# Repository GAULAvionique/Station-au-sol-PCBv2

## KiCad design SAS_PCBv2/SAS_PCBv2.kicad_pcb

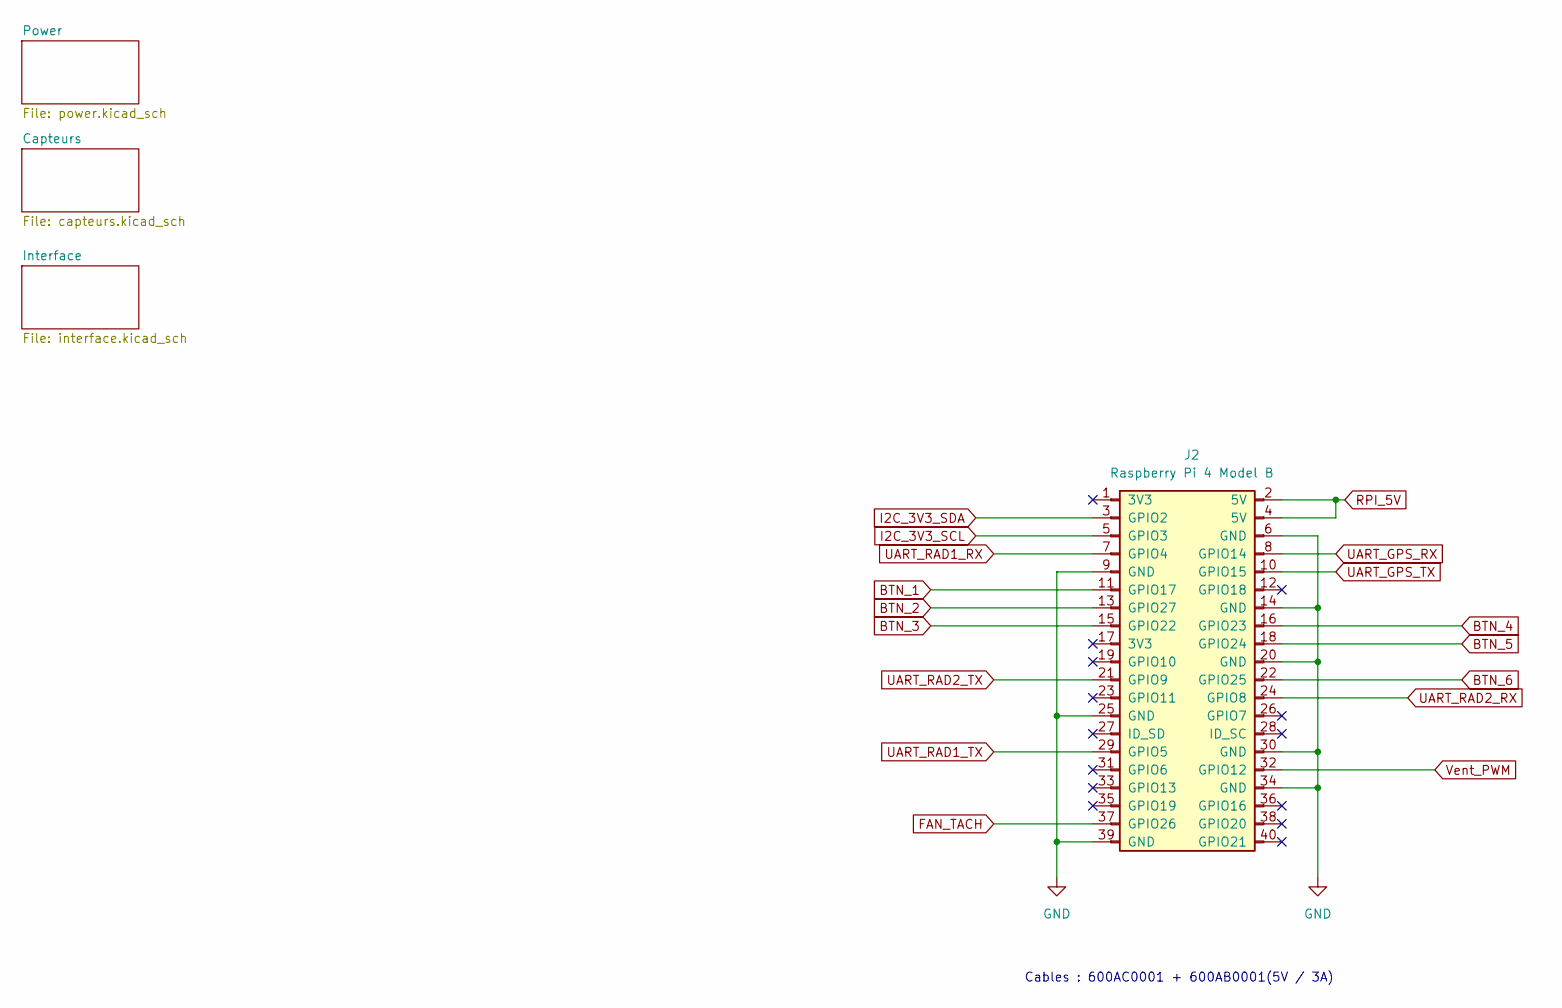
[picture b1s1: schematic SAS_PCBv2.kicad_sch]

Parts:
J2: Raspberry Pi 4 Model B; PinSocket_2x20_P2.54mm_Vertical

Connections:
BTN_1: J2.11 (GPIO17); also elsewhere on the board
BTN_2: J2.13 (GPIO27); also elsewhere on the board
BTN_3: J2.15 (GPIO22); also elsewhere on the board
BTN_4: J2.16 (GPIO23); also elsewhere on the board
BTN_5: J2.18 (GPIO24); also elsewhere on the board
BTN_6: J2.22 (GPIO25); also elsewhere on the board
FAN_TACH: J2.37 (GPIO26); also elsewhere on the board
GND: J2.6 (GND), J2.9 (GND), J2.14 (GND), J2.20 (GND), J2.25 (GND), J2.30 (GND), J2.34 (GND), J2.39 (GND); also elsewhere on the board
I2C_3V3_SCL: J2.5 (GPIO3); also elsewhere on the board
I2C_3V3_SDA: J2.3 (GPIO2); also elsewhere on the board
RPI_5V: J2.2 (5V), J2.4 (5V); also elsewhere on the board
UART_GPS_RX: J2.8 (GPIO14); also elsewhere on the board
UART_GPS_TX: J2.10 (GPIO15); also elsewhere on the board
UART_RAD1_RX: J2.7 (GPIO4); also elsewhere on the board
UART_RAD1_TX: J2.29 (GPIO5); also elsewhere on the board
UART_RAD2_RX: J2.24 (GPIO8); also elsewhere on the board
UART_RAD2_TX: J2.21 (GPIO9); also elsewhere on the board
Vent_PWM: J2.32 (GPIO12); also elsewhere on the board

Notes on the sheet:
Cables : 600AC0001 + 600AB0001(5V / 3A)

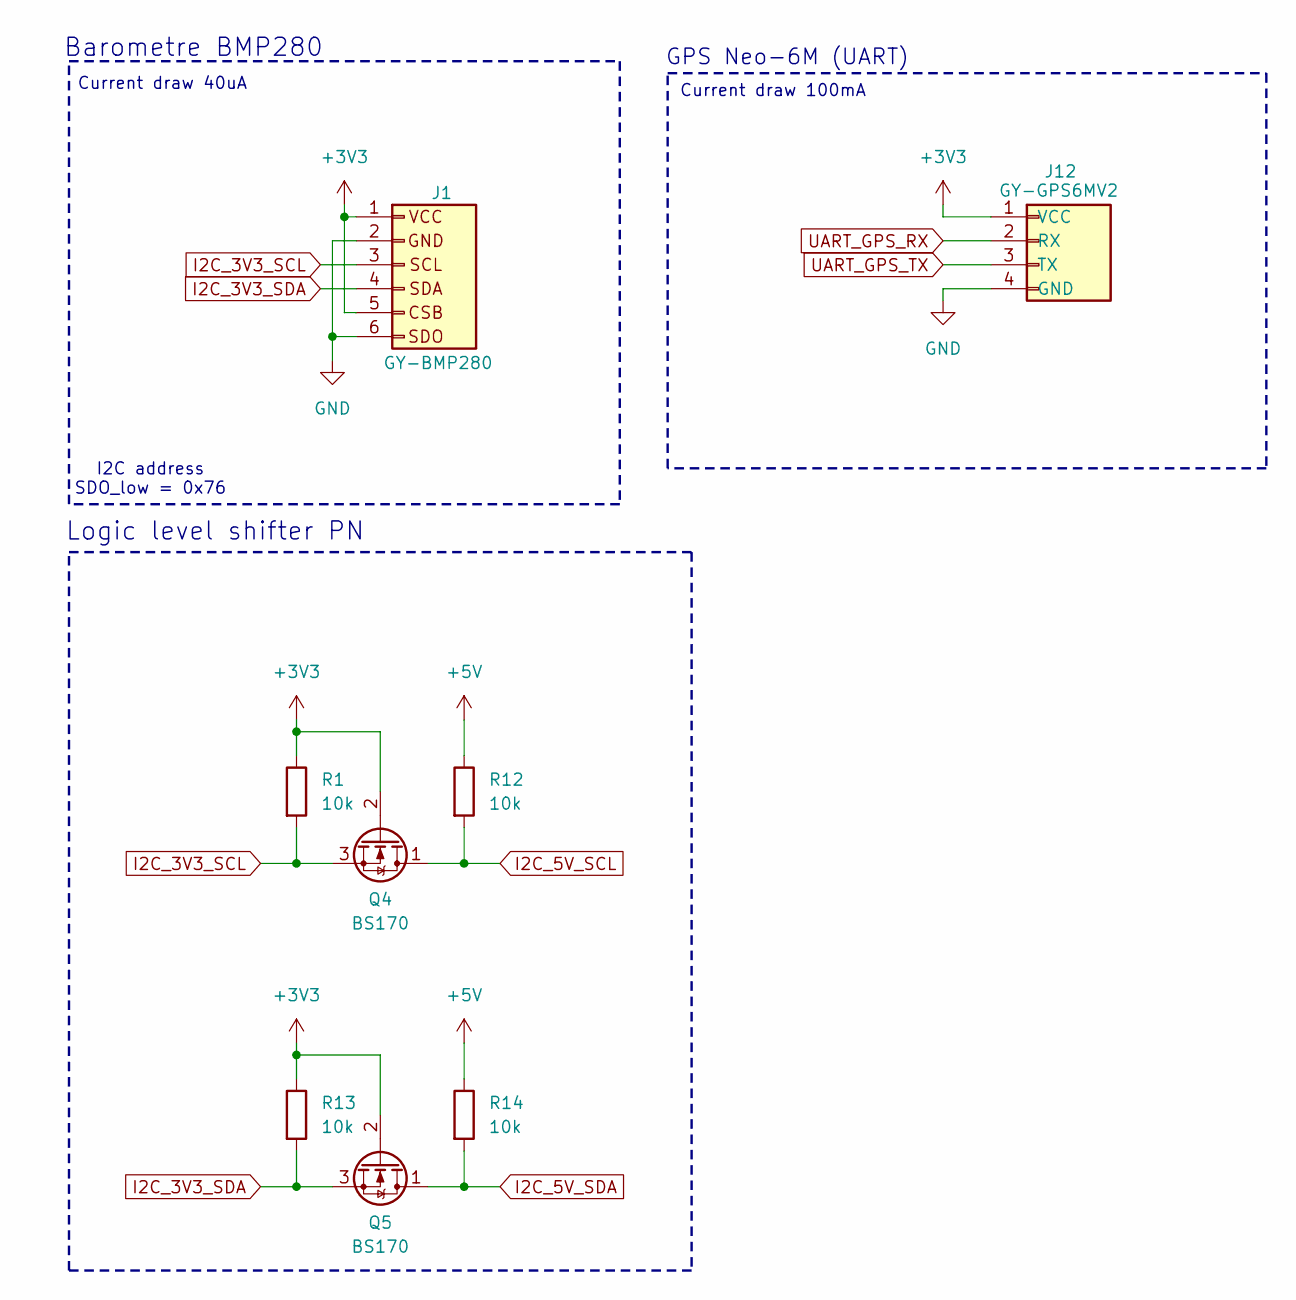
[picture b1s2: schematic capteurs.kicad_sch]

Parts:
J1: GY-BMP280; PinHeader_1x06_P2.54mm_Vertical
J12: GY-GPS6MV2; PinHeader_1x04_P2.54mm_Vertical
Q4, Q5: BS170; TO-92_Inline
R1, R12, R13, R14: 10k; R_Axial_DIN0207_L6.3mm_D2.5mm_P10.16mm_Horizontal; Digikey MFR-25FRF52-10K

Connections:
+3V3: J1.1 (Vcc), J1.5, J12.1 (VCC), Q4.2 (G), Q5.2 (G), R1.1, R13.1; also elsewhere on the board
+5V: R12.1, R14.1; also elsewhere on the board
GND: J1.2, J1.6, J12.4 (GND); also elsewhere on the board
I2C_3V3_SCL: J1.3, Q4.3 (S), R1.2; also elsewhere on the board
I2C_3V3_SDA: J1.4, Q5.3 (S), R13.2; also elsewhere on the board
I2C_5V_SCL: Q4.1 (D), R12.2; also elsewhere on the board
I2C_5V_SDA: Q5.1 (D), R14.2; also elsewhere on the board
UART_GPS_RX: J12.2 (RX); also elsewhere on the board
UART_GPS_TX: J12.3 (TX); also elsewhere on the board

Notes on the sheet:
Current draw 40uA
Logic level shifter PN
GPS Neo-6M (UART)
I2C address SDO_low = 0x76
Barometre BMP280
Current draw 100mA

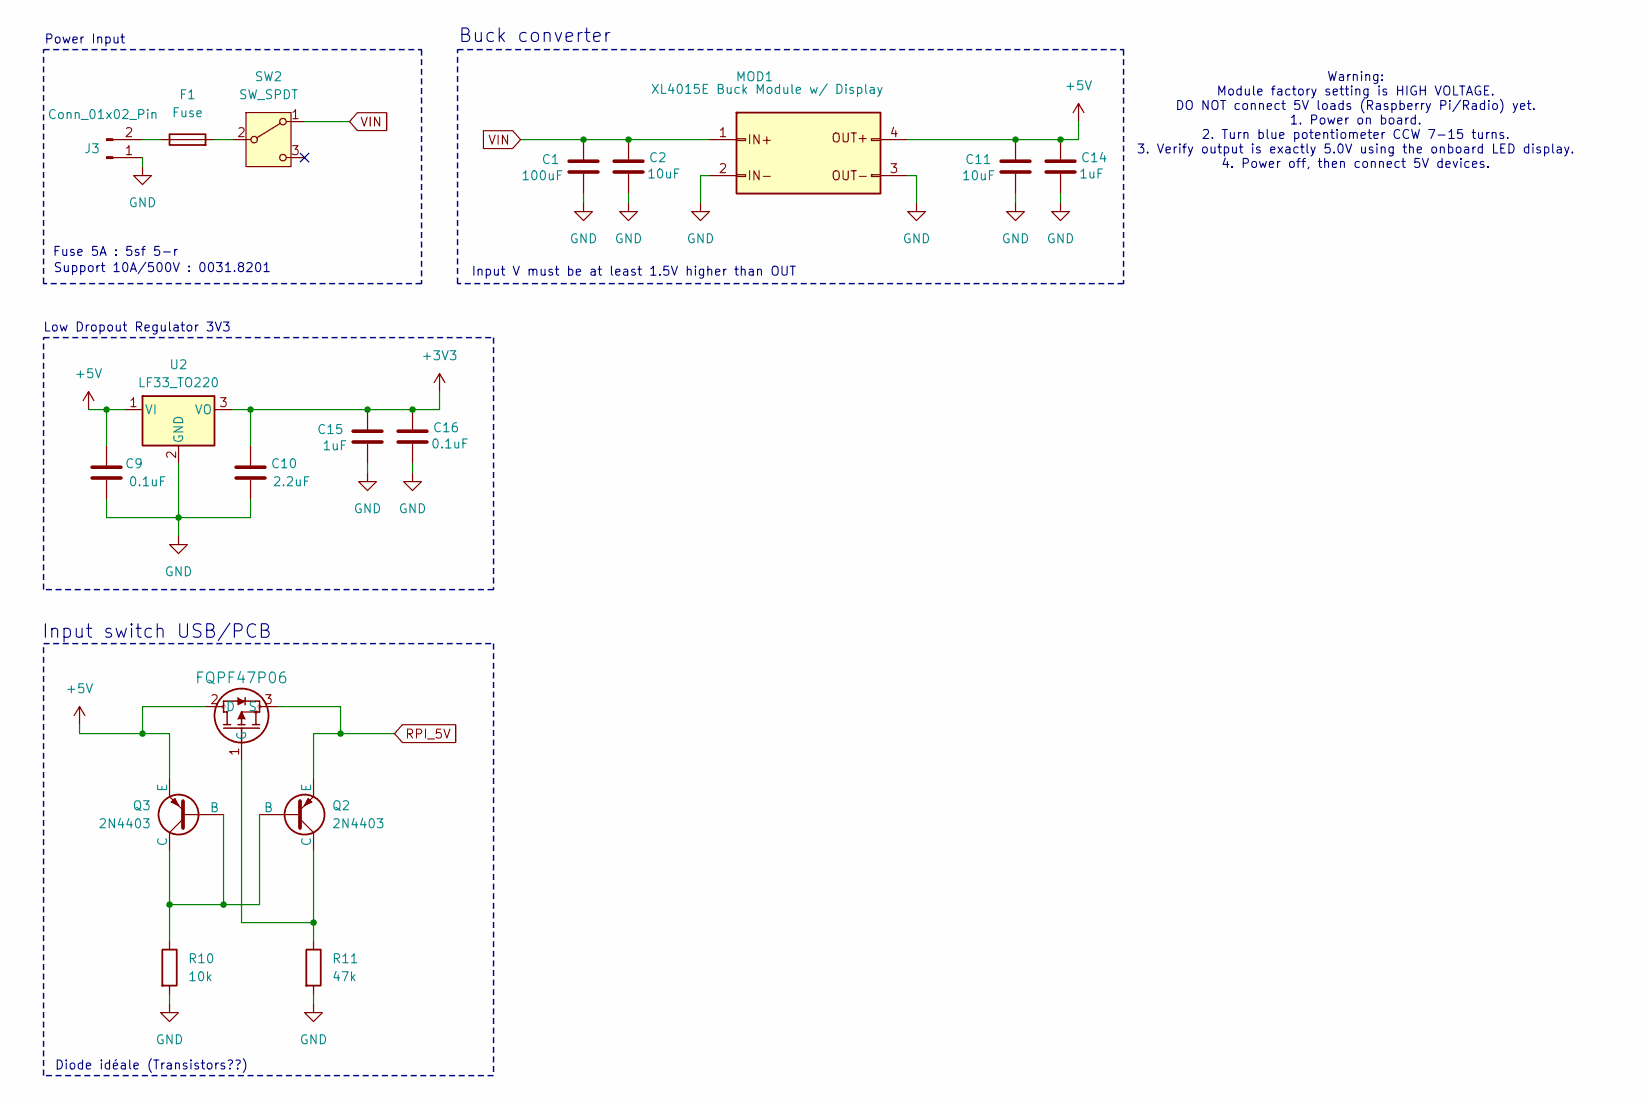
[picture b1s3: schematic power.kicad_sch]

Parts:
C1: 100uF; CAP_RR71_NIC
C2, C11: 10uF; CP_Radial_D5.0mm_P2.00mm; Digikey 1189-2322-ND
C9, C16: 0.1uF; CAP_C320_KEM
C10: 2.2uF; CAP_FG14_TDK
C14, C15: 1uF; CP_Radial_D5.0mm_P2.00mm
F1: Fuse; Fuseholder_Cylinder-5x20mm_Schurter_0031_8201_Horizontal_Op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
J3: Conn_01x02_Pin; AMASS_XT30U-M_1x02_P5.0mm_Vertical
MOD1: XL4015E Buck Module w/ Display; XL4015E_Buck_Module_68x38mm(1)
MOSFET1: FQPF47P06; PMOS_FQP_ONS
Q2, Q3: 2N4403; PBIP_2N4403_DIO
R10: 10k; R_Axial_DIN0207_L6.3mm_D2.5mm_P10.16mm_Horizontal; Digikey MFR-25FRF52-10K
R11: 47k; R_Axial_DIN0207_L6.3mm_D2.5mm_P10.16mm_Horizontal; Digikey MFR-25FRF52-47K
SW2: SW_SPDT; SW_ANT1_CRS
U2: LF33_TO220; TO-220-3_Vertical

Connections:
+3V3: C10.1, C15.1, C16.1, U2.3 (VO); also elsewhere on the board
+5V: C9.1, C11.1, C14.1, MOD1.4 (OUT+), MOSFET1.2 (D), Q3.1 (E), U2.1 (VI); also elsewhere on the board
GND: C1.2, C2.2, C9.2, C10.2, C11.2, C14.2, C15.2, C16.2, J3.1, MOD1.2 (IN-), MOD1.3 (OUT-), R10.2, R11.2, U2.2 (GND); also elsewhere on the board
unnamed: F1.1, J3.2
unnamed: MOSFET1.1 (G), Q2.3 (C), R11.1
unnamed: Q2.2 (B), Q3.2 (B), Q3.3 (C), R10.1
unnamed: F1.2, SW2.2 (B)
RPI_5V: MOSFET1.3 (S), Q2.1 (E); also elsewhere on the board
VIN: C1.1, C2.1, MOD1.1 (IN+), SW2.1 (A)

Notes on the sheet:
Fuse 5A : 5sf 5-r
Low Dropout Regulator 3V3
Support 10A/500V : 0031.8201
Diode idéale (Transistors??)
Input switch USB/PCB
Input V must be at least 1.5V higher than OUT
Power Input
Buck converter
Warning: Module factory setting is HIGH VOLTAGE. DO NOT connect 5V loads (Raspberry Pi/Radio) yet. 1. Power on board. 2. Turn blue potentiometer CCW 7-15 turns. 3. Verify output is exactly 5.0V using the onboard LED display. 4. Power off, then connect 5V devices.

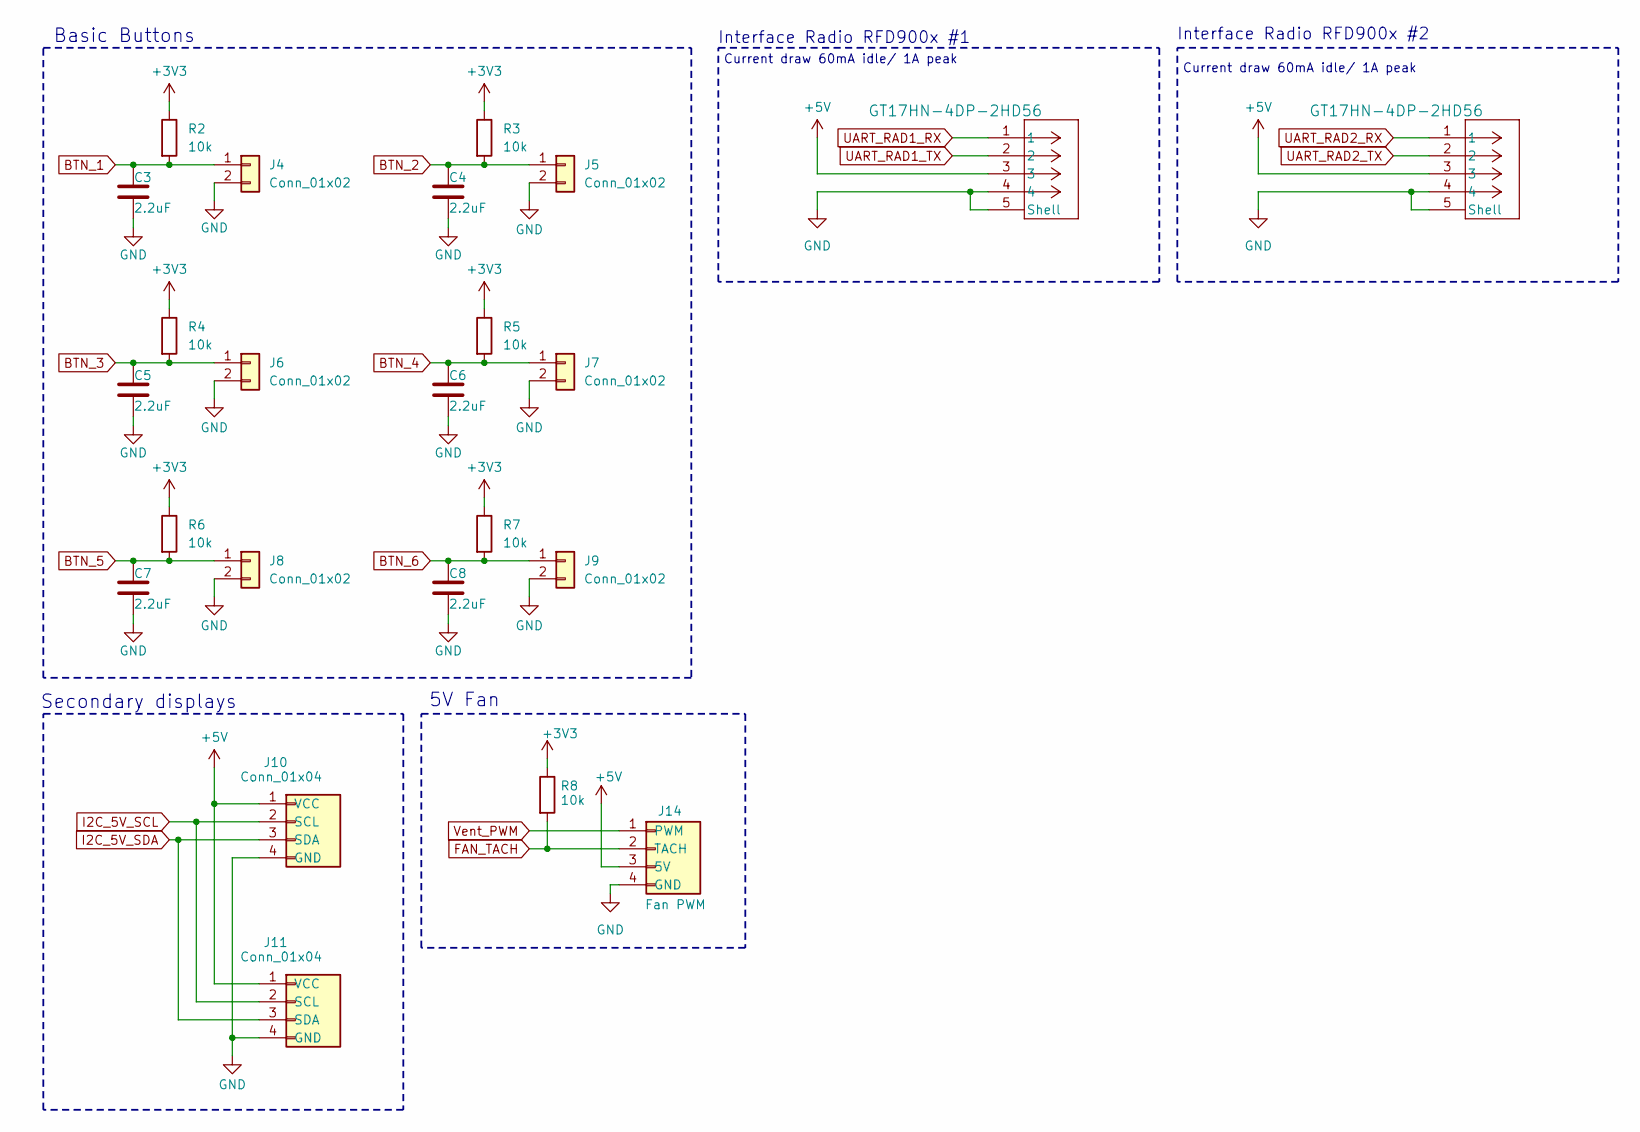
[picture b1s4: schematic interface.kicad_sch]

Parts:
C3, C4, C5, C6, C7, C8: 2.2uF; CAP_FG14_TDK
J4, J5, J6, J7, J8, J9: Conn_01x02; PinHeader_1x02_P2.54mm_Vertical
J10, J11: Conn_01x04; PinHeader_1x04_P2.54mm_Vertical
J14: Fan PWM; PinHeader_1x04_P2.54mm_Vertical
J16, J17: GT17HN-4DP-2HD56; CONN4_GT17HN_HIR; Manufacturer_Part_Number GT17HN-4DP-2H(D)(56); DigiKey_Part_Number 26-GT17HN-4DP-2H(D)(56)-ND
R2, R3, R4, R5, R6, R7, R8: 10k; R_Axial_DIN0207_L6.3mm_D2.5mm_P10.16mm_Horizontal; Digikey MFR-25FRF52-10K

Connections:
+3V3: R2.1, R3.1, R4.1, R5.1, R6.1, R7.1, R8.1; also elsewhere on the board
+5V: J10.1 (VCC), J11.1 (VCC), J14.3 (5V), J16.3, J17.3; also elsewhere on the board
BTN_1: C3.1, J4.1, R2.2; also elsewhere on the board
BTN_2: C4.1, J5.1, R3.2; also elsewhere on the board
BTN_3: C5.1, J6.1, R4.2; also elsewhere on the board
BTN_4: C6.1, J7.1, R5.2; also elsewhere on the board
BTN_5: C7.1, J8.1, R6.2; also elsewhere on the board
BTN_6: C8.1, J9.1, R7.2; also elsewhere on the board
FAN_TACH: J14.2 (TACH), R8.2; also elsewhere on the board
GND: C3.2, C4.2, C5.2, C6.2, C7.2, C8.2, J4.2, J5.2, J6.2, J7.2, J8.2, J9.2, J10.4 (GND), J11.4 (GND), J14.4 (GND), J16.4, J16.5 (Shell), J16.6 (Shell), J16.7 (Shell), J16.8 (Shell), J17.4, J17.5 (Shell), J17.6 (Shell), J17.7 (Shell), J17.8 (Shell); also elsewhere on the board
I2C_5V_SCL: J10.2 (SCL), J11.2 (SCL); also elsewhere on the board
I2C_5V_SDA: J10.3 (SDA), J11.3 (SDA); also elsewhere on the board
UART_RAD1_RX: J16.1; also elsewhere on the board
UART_RAD1_TX: J16.2; also elsewhere on the board
UART_RAD2_RX: J17.1; also elsewhere on the board
UART_RAD2_TX: J17.2; also elsewhere on the board
Vent_PWM: J14.1 (PWM); also elsewhere on the board

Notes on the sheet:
5V Fan
Current draw 60mA idle/ 1A peak
Secondary displays
Interface Radio RFD900x #2
Basic Buttons
Interface Radio RFD900x #1

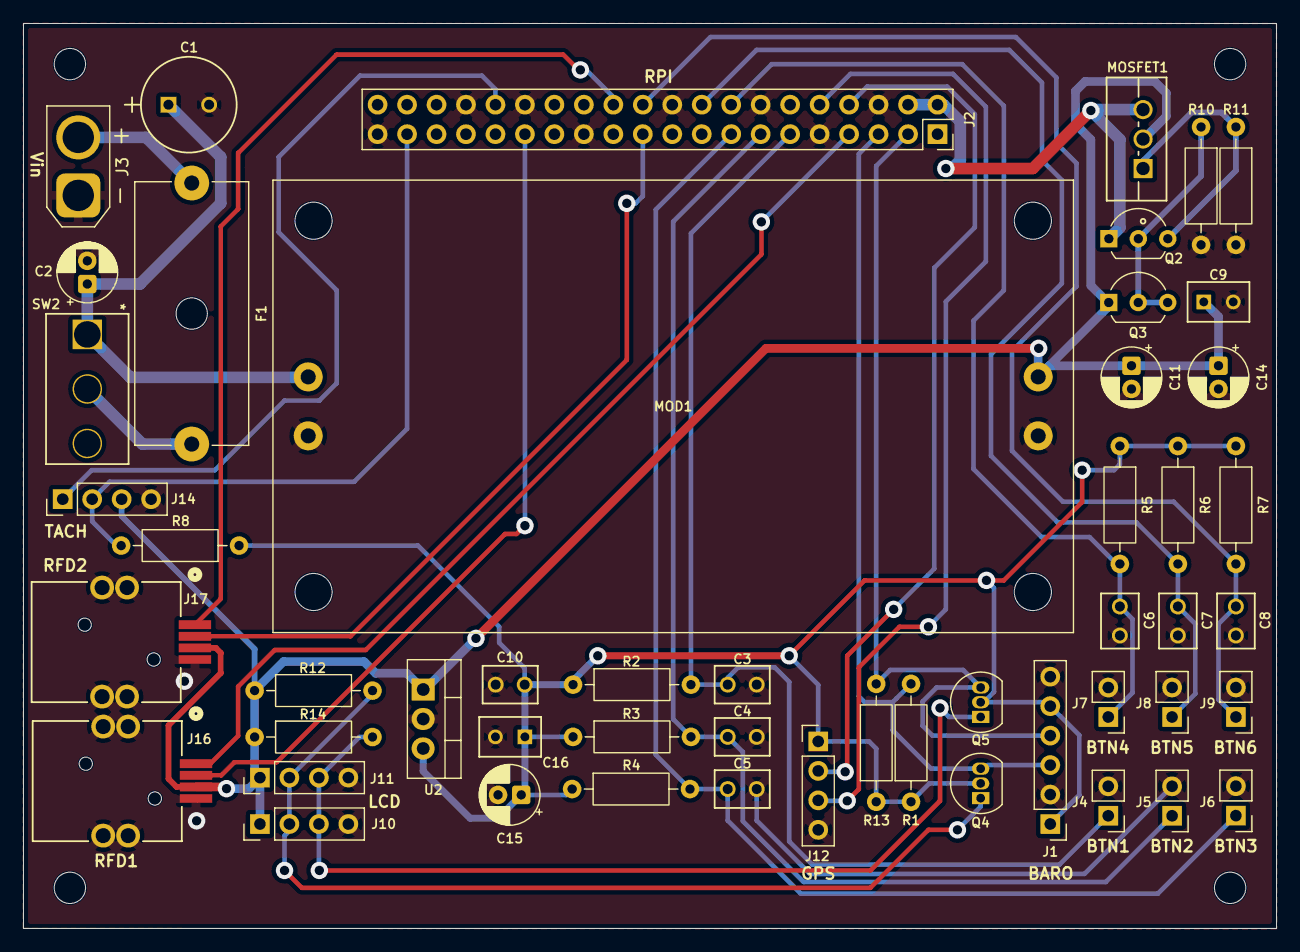
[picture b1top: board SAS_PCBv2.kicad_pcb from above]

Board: 2 copper layers, 108.0 x 78.0 mm, 51 parts (0 on the bottom side), 27 nets.

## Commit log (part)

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2025-10-13 création projet kicad
2025-10-30 Add footprint to create folder
2026-01-10 bmp280 + LogicLevelShifterPN I2C
2026-01-21 Power Input and LDO
2026-03-03 Added basic Buttons w/ Rpi connections
2026-03-03 Added secondary displays, completed LDO 3V3
2026-03-04 Radio et GPS fait selon les datasheets normalement
2026-03-05 debut buck
2026-04-16 schematic sans error et le debut de pcb
2026-05-07 Correction UART5 -> UART3, ajout d'un ventilateur 12V PWM
2026-05-08 Switch USB/PCB, connections Power, spam condensateurs, resistance pull-up
2026-05-12 LDO du service, Logic level shifter custom
2026-05-12 Amélioration des modèles Rpi et page power, switch PCB/USB fonctionnelle
2026-05-13 Identification des transistors, footprint BMP280 et GPS Neo-6M, correction du fan PWM
2026-05-28 Ajout du connecteur spécial pour les radios, insertion des footprints dans le PCB, fin du schéma
2026-05-28 Composantes placees sur le PCB
2026-05-29 PCB prêt à être routé
